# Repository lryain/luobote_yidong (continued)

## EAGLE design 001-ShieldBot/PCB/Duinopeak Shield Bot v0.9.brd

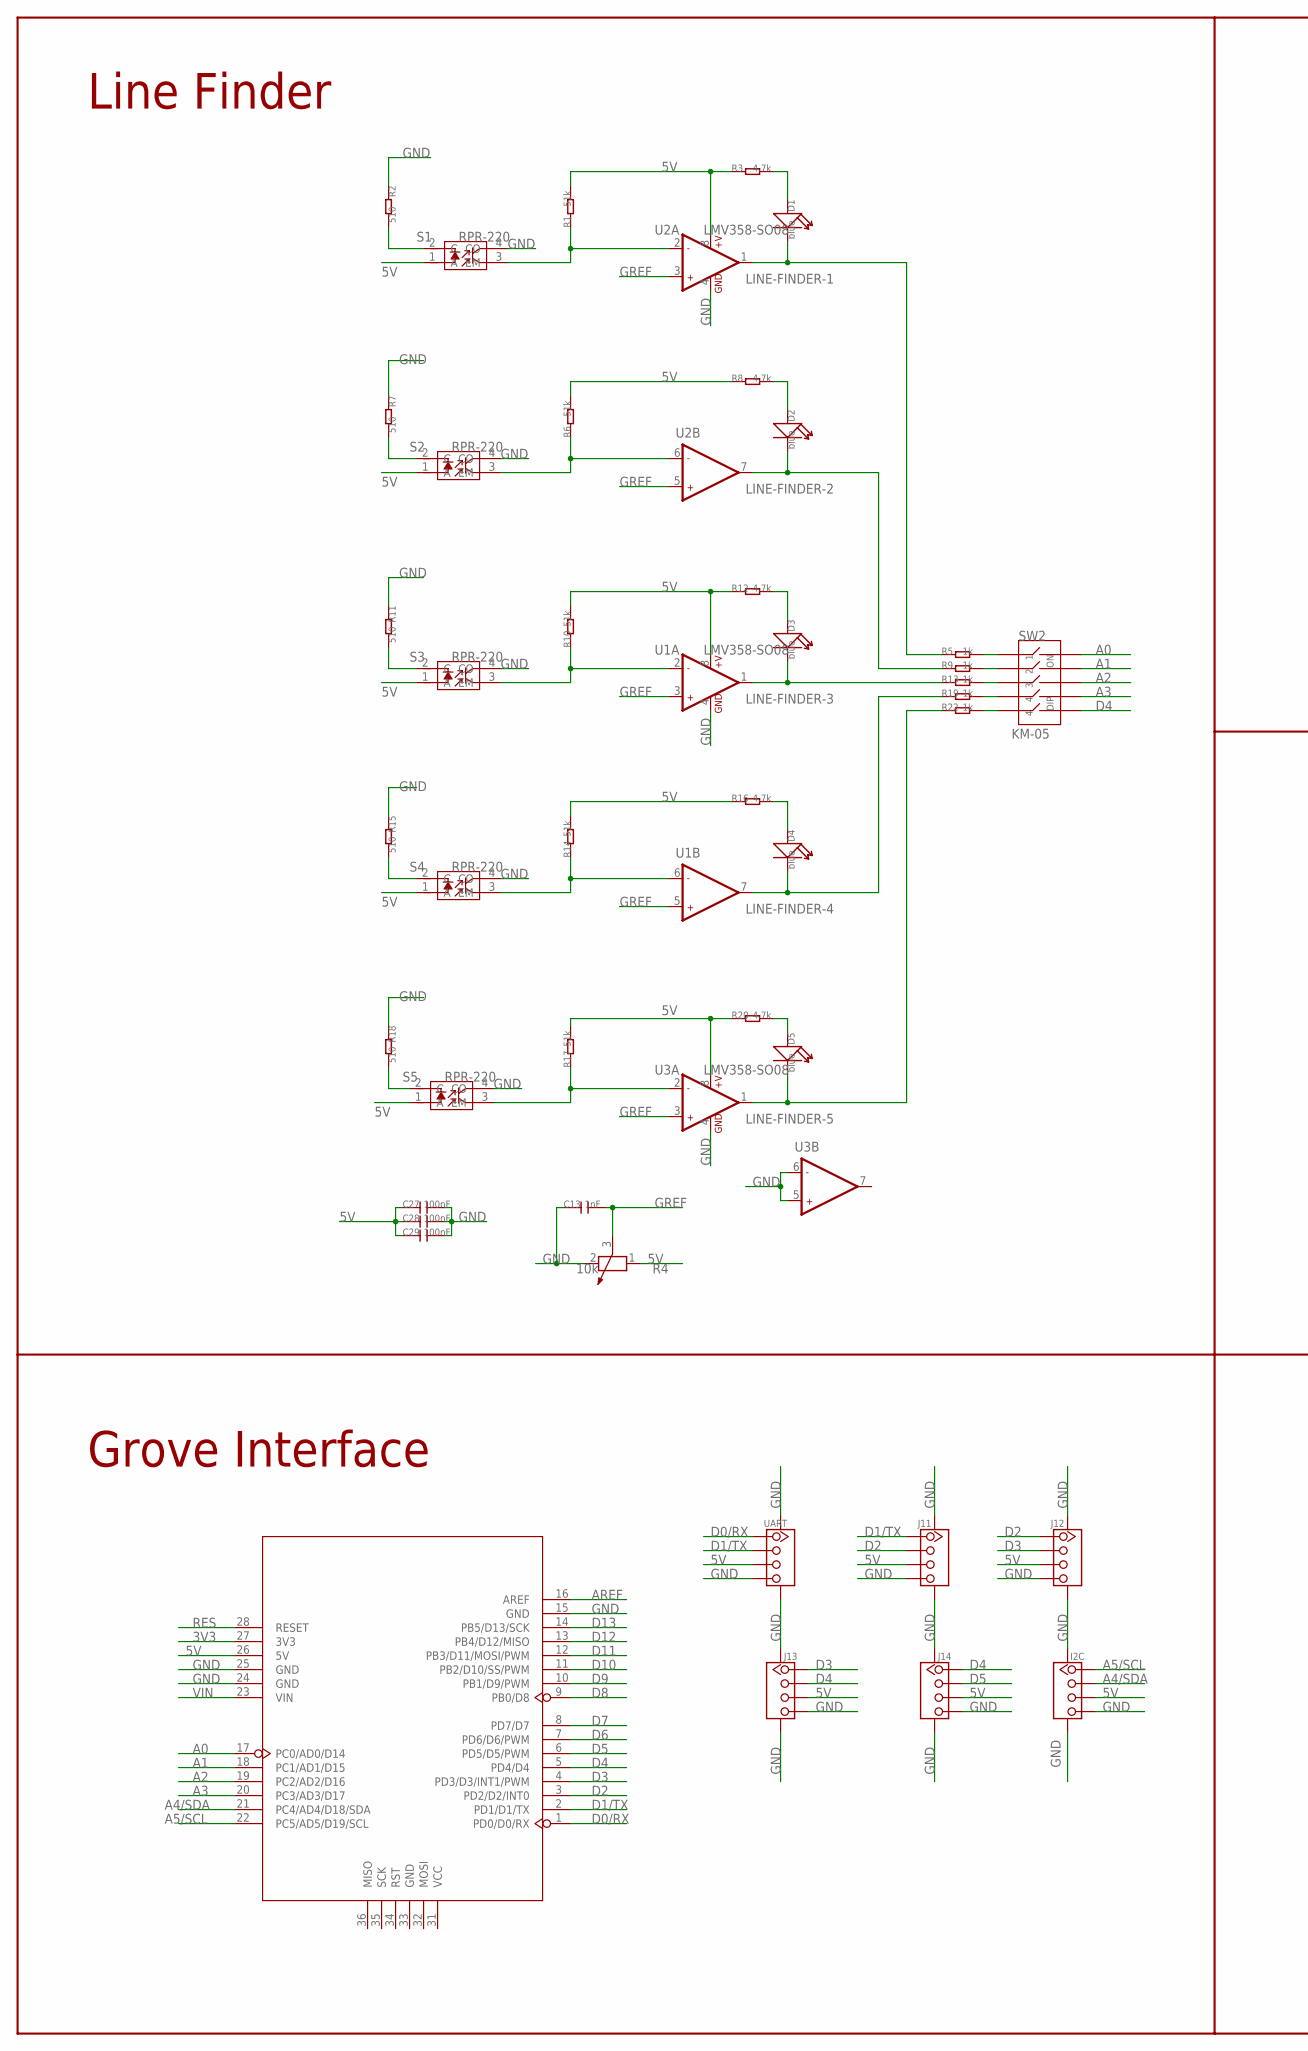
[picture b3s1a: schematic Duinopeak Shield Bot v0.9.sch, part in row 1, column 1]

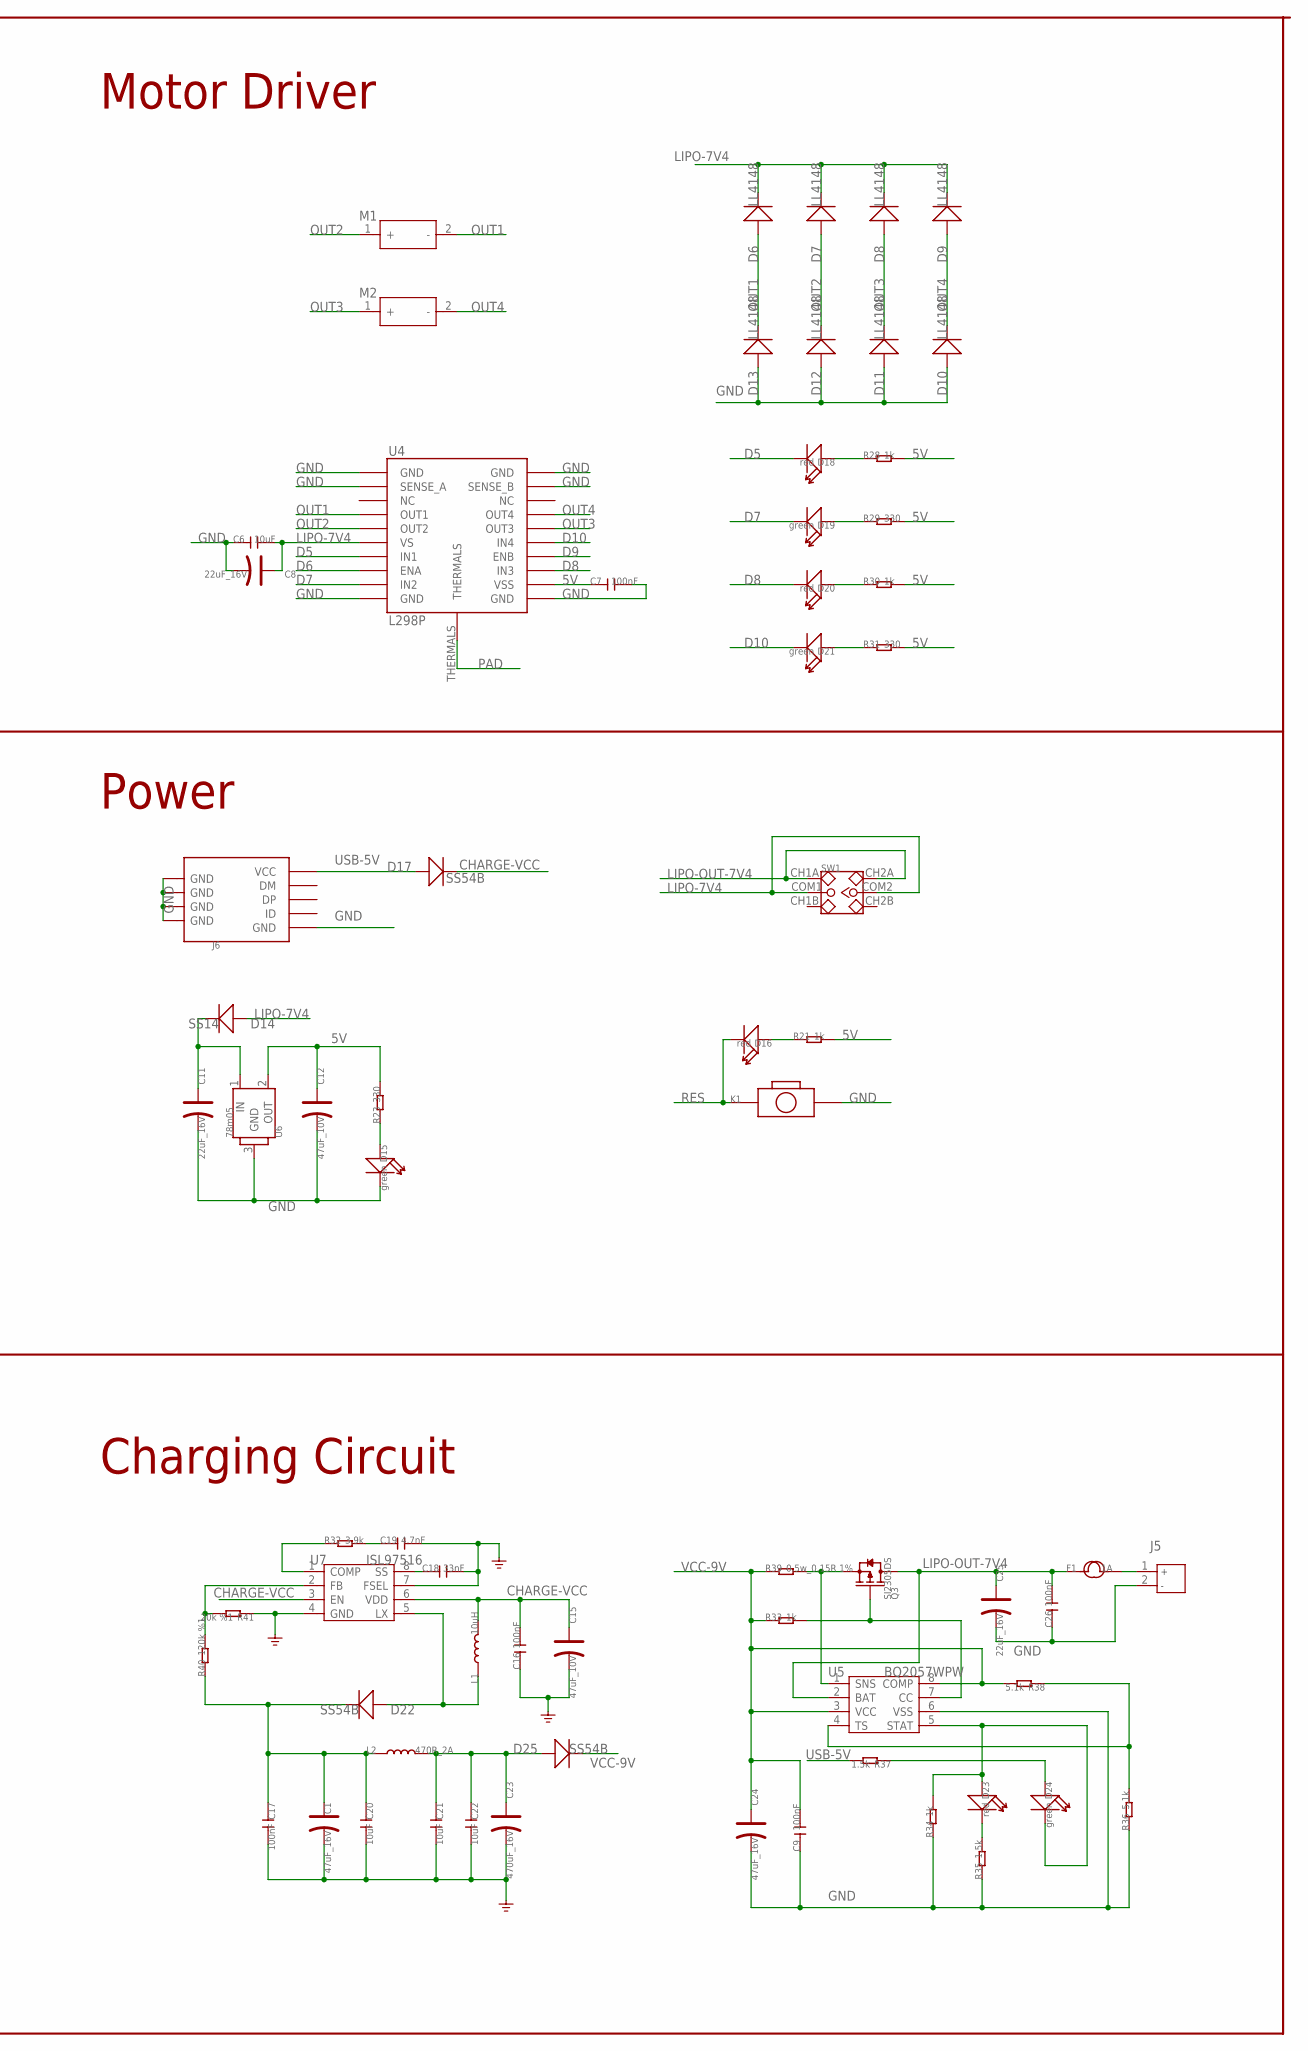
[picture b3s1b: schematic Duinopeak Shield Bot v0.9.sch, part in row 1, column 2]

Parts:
C1, C24: 47uF_16V; AVX-C
C6, C20, C21, C22: 10uF; C0603
C7, C9, C16, C17, C26, C27, C28, C29: 100nF; C0603
C8, C11, C25: 22uF_16V; AVX-B
C12, C15: 47uF_10V; AVX-B
C13: 1nF; C0603
C18: 33nF; C0603
C19: 4.7nF; C0603
C23: 470uF_16V; AVX-E
D1, D2, D3, D4, D5: blue; LED-0603
D6, D7, D8, D9, D10, D11, D12, D13: LL4148; SOD123
D14: SS14; D2010
D15, D19, D21, D24: green; LED-0603
D16, D18, D20, D23: red; LED-0603
D17, D22, D25: SS54B; SMB
F1: 1A; 1812
I2C: TWIG-4P-2.0-SMD-FEMALE-REINFORCE'90D'; 4P-SMD-2.0-90D
J5: JACK-JST-2P-PW'2.0'; JST-2.0
J6: USB-MINIUSB-5P-STRONG; MINI-SMD-5P
J11, J12, J13, J14: TWIG-4P-2.0-SMD-FEMALE-REINFORCE'90D'; 4P-SMD-2.0-90D
K1: BOTTON-2P-90D; 2P-7.62X3.56-90D
L1: 10uH; 2626
L2: 470R_2A; L0805
M1, M2: MOTOR-2P-PAD; 2P-SMD-27X26
Q3: SI2305DS; SOT23
R1, R6, R10, R14, R17: 51k; R0603
R2, R7, R11, R15, R18: 510; R0603
R3, R8, R12, R16, R20: 4.7k; R0603
R4: 10k; 3P-SQUA-7X6.8
R5, R9, R13, R19, R21, R22, R28, R30, R33, R34: 1k; R0603
R23, R29, R31: 330; R0603
R32: 3.9k; R0603
R35, R37: 1.5k; R0603
R36, R38: 5.1k; R0603
R39: 0.5w_0.15R 1%; R2512
R40: 120k %1; R0603
R41: 20k %1; R0603
S1, S2, S3, S4, S5: RPR-220; 4P-6.4X4.9X6.5H
SW1: SWITCH-2CH-6P'90D'; 6P-2CH-2.54-9.0X3.6-90D
SW2: KM-05; 10P-SMD-14.2X6.8
U1, U2, U3: LMV358-SO08; SO08
U4: L298P; POWERSO20
U5: BQ2057WPW; TSSOP8
U6: 78m05; TO252
U7: ISL97516; MSOP8
U13: ARDUINO
UART: TWIG-4P-2.0-SMD-FEMALE-REINFORCE'90D'; 4P-SMD-2.0-90D

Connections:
3V3: U13.27 (3V3)
5V: C7.1, C12.+, C27.1, C28.1, C29.1, I2C.3, J11.3, J12.3, J13.3, J14.3, R1.2, R3.1, R4.1, R6.2, R8.1, R10.2, R12.1, R14.2, R16.1, R17.2, R20.1, R21.2, R23.2, R28.2, R29.2, R30.2, R31.2, S1.1 (A), S2.1 (A), S3.1 (A), S4.1 (A), S5.1 (A), U1.8 (+V), U2.8 (+V), U3.8 (+V), U4.P$12 (VSS), U6.2 (OUT), U13.26 (5V), UART.3
A0: SW2.10, U13.17 (PC0/AD0/D14)
A1: SW2.9, U13.18 (PC1/AD1/D15)
A2: SW2.8, U13.19 (PC2/AD2/D16)
A3: SW2.7, U13.20 (PC3/AD3/D17)
A4/SDA: I2C.2, U13.21 (PC4/AD4/D18/SDA)
A5/SCL: I2C.1, U13.22 (PC5/AD5/D19/SCL)
AREF: U13.16 (AREF)
CHARGE-VCC: C15.+, C16.2, D17.-, L1.2, U7.3 (EN), U7.6 (VDD)
D0/RX: U13.1 (PD0/D0/RX), UART.1
D1/TX: J11.1, U13.2 (PD1/D1/TX), UART.2
D2: J11.2, J12.1, U13.3 (PD2/D2/INT0)
D3: J12.2, J13.1, U13.4 (PD3/D3/INT1/PWM)
D4: J13.2, J14.1, SW2.6, U13.5 (PD4/D4)
D5: D18.-, J14.2, U4.P$7 (IN1), U13.6 (PD5/D5/PWM)
D6: U4.P$8 (ENA), U13.7 (PD6/D6/PWM)
D7: D19.-, U4.P$9 (IN2), U13.8 (PD7/D7)
D8: D20.-, U4.P$13 (IN3), U13.9 (PB0/D8)
D9: U4.P$14 (ENB), U13.10 (PB1/D9/PWM)
D10: D21.-, U4.P$15 (IN4), U13.11 (PB2/D10/SS/PWM)
D11: U13.12 (PB3/D11/MOSI/PWM)
D12: U13.13 (PB4/D12/MISO)
D13: U13.14 (PB5/D13/SCK)
GND: C1.-, C6.1, C7.2, C8.-, C9.1, C11.-, C12.-, C13.1, C15.-, C16.1, C17.2, C18.2, C19.2, C20.2, C21.2, C22.2, C23.-, C24.-, C25.-, C26.1, C27.2, C28.2, C29.2, D10.+, D11.+, D12.+, D13.+, D15.-, I2C.4, I2C.SS1, I2C.SS2, J5.2, J6.5 (GND), J6.GND@1 (GND), J6.GND@2 (GND), J6.GND@3 (GND), J6.GND@4 (GND), J11.4, J11.SS1, J11.SS2, J12.4, J12.SS1, J12.SS2, J13.4, J13.SS1, J13.SS2, J14.4, J14.SS1, J14.SS2, K1.P$2 (2), R2.1, R4.2, R7.1, R11.1, R15.1, R18.1, R34.1, R35.1, R36.1, R41.1, S1.4 (CO), S2.4 (CO), S3.4 (CO), S4.4 (CO), S5.4 (CO), U1.4 (GND), U2.4 (GND), U3.4 (GND), U3.5 (+IN2), U3.6 (-IN2), U4.P$1 (GND), U4.P$2 (SENSE_A), U4.P$10 (GND), U4.P$11 (GND), U4.P$19 (SENSE_B), U4.P$20 (GND), U5.6 (VSS), U6.3 (GND), U7.4 (GND), U7.7 (FSEL), U13.15 (GND), U13.24 (GND), U13.25 (GND), UART.4, UART.SS1, UART.SS2
GREF: C13.2, R4.3, U1.3 (+IN1), U1.5 (+IN2), U2.3 (+IN1), U2.5 (+IN2), U3.3 (+IN1)
LINE-FINDER-1: D1.-, R5.1, U2.1 (OUT1)
LINE-FINDER-2: D2.-, R9.1, U2.7 (OUT2)
LINE-FINDER-3: D3.-, R13.1, U1.1 (OUT1)
LINE-FINDER-4: D4.-, R19.1, U1.7 (OUT2)
LINE-FINDER-5: D5.-, R22.1, U3.1 (OUT1)
LIPO-7V4: C6.2, C8.+, D6.-, D7.-, D8.-, D9.-, D14.+, SW1.COM1, SW1.COM2, U4.P$6 (VS)
LIPO-OUT-7V4: C25.+, C26.2, F1.1, Q3.3 (D), SW1.CH1A, SW1.CH2A, U5.2 (BAT)
unnamed: D18.+, R28.1
unnamed: R1.1, S1.3 (EM), U2.2 (-IN1)
unnamed: R6.1, S2.3 (EM), U2.6 (-IN2)
unnamed: D2.+, R8.2
unnamed: R2.2, S1.2 (C)
unnamed: R7.2, S2.2 (C)
unnamed: D19.+, R29.1
unnamed: R10.1, S3.3 (EM), U1.2 (-IN1)
unnamed: D3.+, R12.2
unnamed: R11.2, S3.2 (C)
unnamed: D20.+, R30.1
unnamed: D1.+, R3.2
unnamed: R15.2, S4.2 (C)
unnamed: D4.+, R16.2
unnamed: R5.2, SW2.1
unnamed: F1.2, J5.1
unnamed: R9.2, SW2.2
unnamed: D5.+, R20.2
unnamed: R18.2, S5.2 (C)
unnamed: R17.1, S5.3 (EM), U3.2 (-IN1)
unnamed: R13.2, SW2.3
unnamed: R19.2, SW2.4
unnamed: R22.2, SW2.5
unnamed: D16.+, R21.1
unnamed: D21.+, R31.1
unnamed: D15.+, R23.1
unnamed: Q3.2 (S), R39.2, U5.1 (SNS)
unnamed: R14.1, S4.3 (EM), U1.6 (-IN2)
unnamed: Q3.1 (G), R33.2, U5.7 (CC)
unnamed: D23.-, R35.2
unnamed: R36.2, R38.1, U5.4 (TS)
unnamed: D23.+, D24.-, R34.2, U5.5 (STAT)
unnamed: D24.+, R37.1
unnamed: C18.1, U7.8 (SS)
unnamed: R40.2, R41.2, U7.2 (FB)
unnamed: D22.+, L1.1, U7.5 (LX)
unnamed: R32.1, U7.1 (COMP)
unnamed: C19.1, R32.2
unnamed: C11.+, D14.-, U6.1 (IN)
OUT1: D6.+, D13.-, M1.2 (-), U4.P$4 (OUT1)
OUT2: D7.+, D12.-, M1.1 (+), U4.P$5 (OUT2)
OUT3: D8.+, D11.-, M2.1 (+), U4.P$16 (OUT3)
OUT4: D9.+, D10.-, M2.2 (-), U4.P$17 (OUT4)
OUTPUT: C1.+, C17.1, C20.1, D22.-, L2.1, R40.1
OUTPUT2: C21.1, C22.1, C23.+, D25.+, L2.2
PAD: U4.THERMALS
RES: D16.-, K1.P$1 (1), U13.28 (RESET)
USB-5V: D17.+, J6.1 (VCC), R37.2
VCC-9V: C9.2, C24.+, D25.-, R33.1, R38.2, R39.1, U5.3 (VCC), U5.8 (COMP)
VIN: U13.23 (VIN)

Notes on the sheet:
Line Finder
Motor Driver
Grove Interface
Charging Circuit
Power

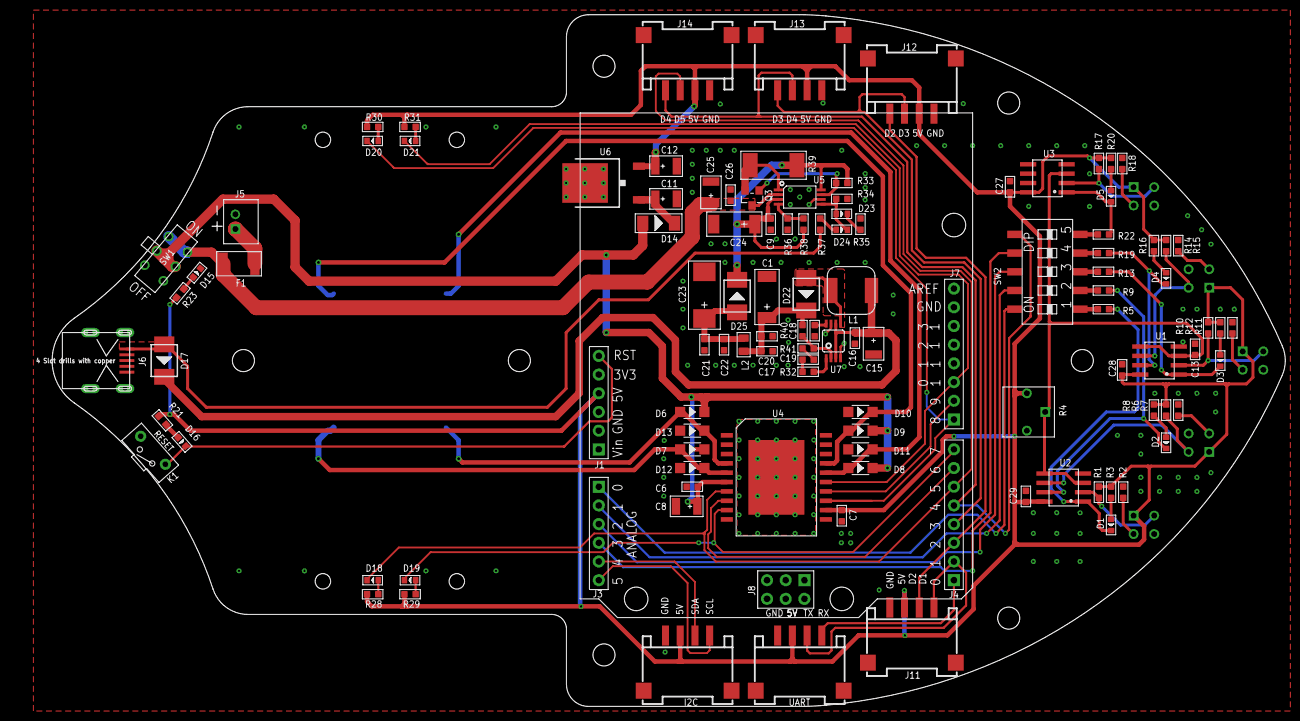
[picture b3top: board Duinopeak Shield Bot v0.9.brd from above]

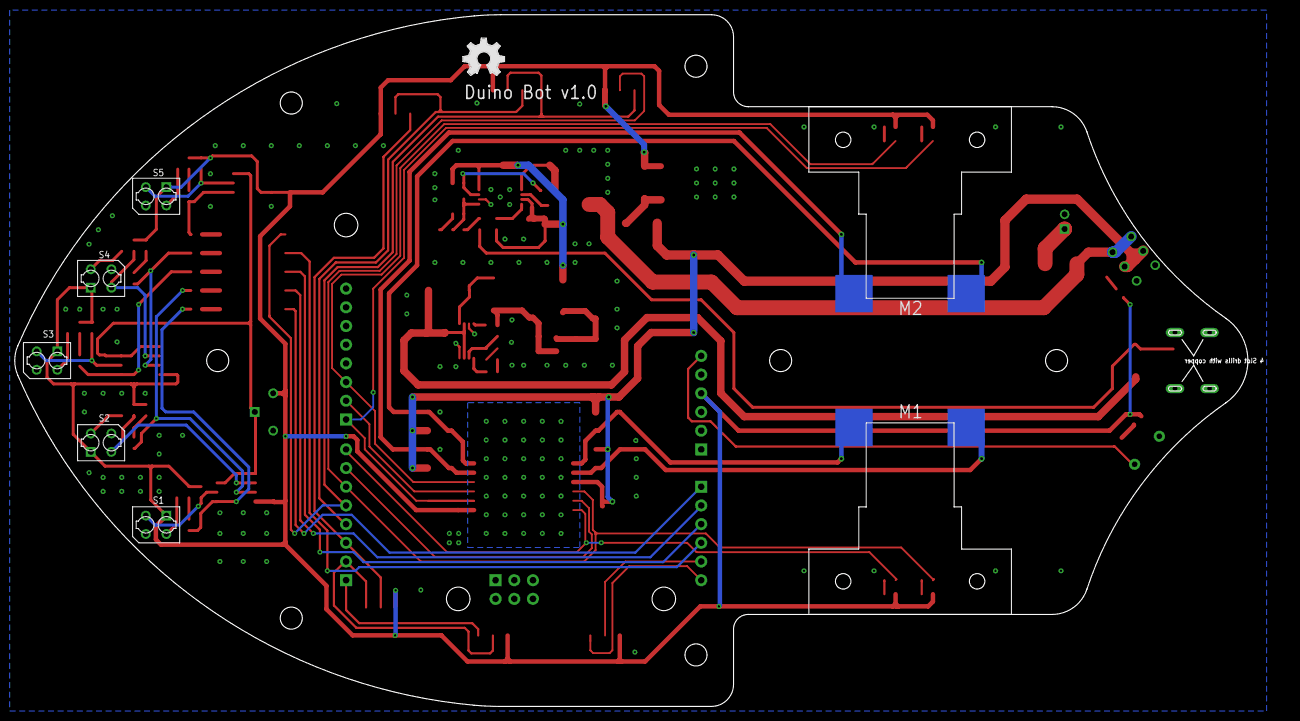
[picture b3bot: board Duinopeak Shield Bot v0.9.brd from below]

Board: 2 copper layers, 167.6 x 94.0 mm, 116 parts (8 on the bottom side), 76 nets.

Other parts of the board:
U$2: OSHW_FILLX200_NOTEXT

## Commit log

2016-12-17 001-ShieldBot
2016-12-17 002-MazeBot
2016-12-22 003-DuinopeakRobot
2016-12-22 004-BalanBot
